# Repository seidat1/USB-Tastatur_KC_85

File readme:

#USB to KC 85

Dies ist ein Adapter, um eine USB-Tastatur an einen KC 85/2..5 anzuschließen.
Es ist mit diesem Adapter auch möglich ein Bluethoos-Tastatur zu betreiben.
Am KC 85 ist keine Änderung notwendig. Es werden die Signale der Originaltastatur nachgebildet.
Dies ergibt eine Flexibilität, wie sie bei der bisherigen Tastatur nicht möglich war. Jeder Taste und jeder Tastenkombination kann ein beliebiges Zeichen oder sogar beliebige Zeichenketten mit Steuerzeichen zugeordnet werden.

Grundlage dieses Adapters ist ein WEMOS D1 mini, der einen ESP8266 Mikroprozessor beinhaltet.
Der USB-Anschluss wird mit einem USB-Host Shield realisiert. 

Die Tastatursignale werden per USB an den USB-Host-Adapter gesendet und von dort per SPI an den Mikroprozessor weitergeleitet. Dieser erzeugt dann das Signal der KC-Tastatur und gibt dieses an den Tastaturstecker ab.
Die Tastencodes und Zeichenketten sind in einer Tastaturtabelle hinterlegt. Diese hat folgenden Aufbau:
	# große Buchstaben
	[CharTable]		# char 'A'
	KeyCnt	= 0x02
	CntMask	= 0xFF
	KeyCode	= 0x04
	Strg	= "A"
	.
	.
	.

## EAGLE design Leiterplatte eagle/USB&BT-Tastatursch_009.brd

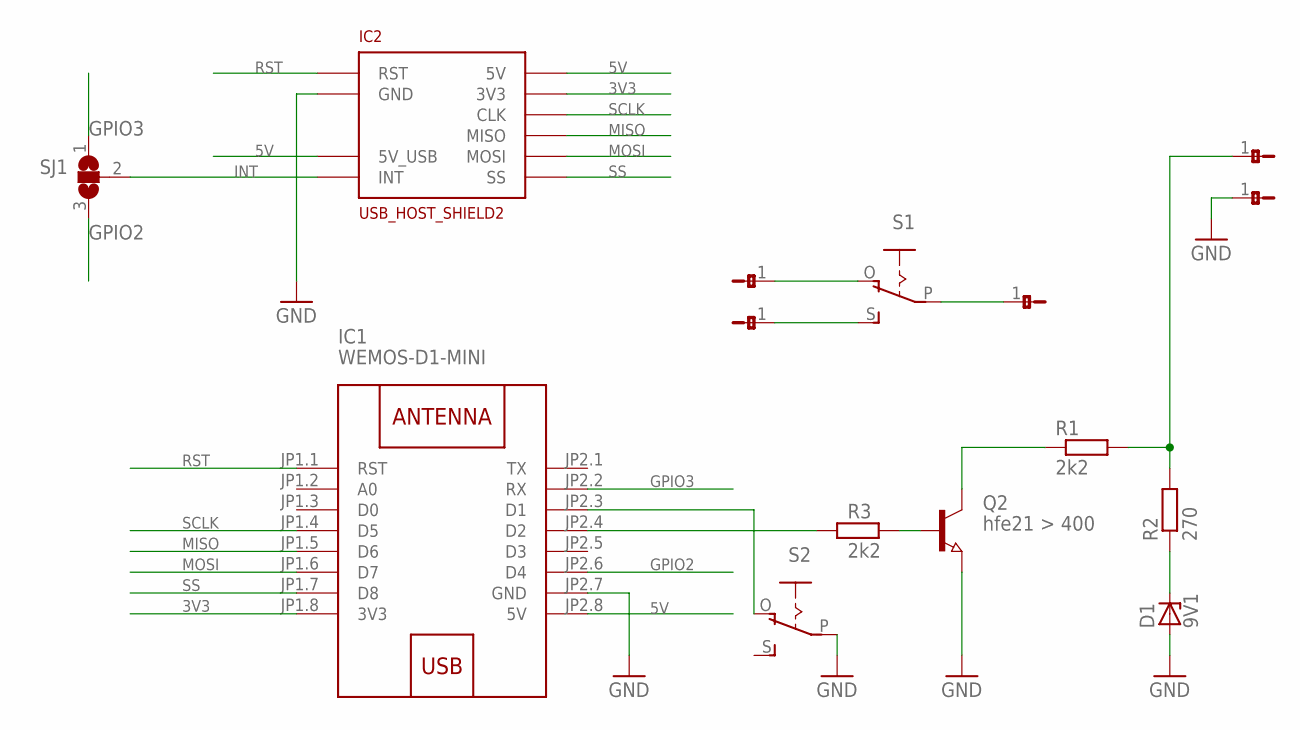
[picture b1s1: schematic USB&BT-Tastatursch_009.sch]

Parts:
D1: 9V1; DO34Z7
IC1: WEMOS-D1-MINI; WEMOS-D1-MINI_PUR
IC2: USB_HOST_SHIELD2; USB_HOST_SHIELD_2
Q2: hfe21 > 400; SOT23W
R1, R3: 2k2; M0805
R2: 270; M0805
S1, S2: EG1218S; EG1218
SJ1: SJ2WSJ_2B; SJ_2B
U$2, U$3, U$4, U$5, U$6: JP1-1JP1-1C; JP1-1C

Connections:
3V3: IC1.JP1.8 (3V3), IC2.VCC (3V3)
5V: IC1.JP2.8 (5V), IC2.5V, IC2.5V_USB
GND: D1.A, IC1.JP2.7 (GND), IC2.GND, IC2.GND@1 (GND), Q2.3 (E), S2.P, U$3.1
GPIO2: IC1.JP2.6 (D4), SJ1.3
GPIO3: IC1.JP2.2 (RX), SJ1.1
INT: IC2.INT, SJ1.2
MISO: IC1.JP1.5 (D6), IC2.MISO
MOSI: IC1.JP1.6 (D7), IC2.MOSI
unnamed: IC1.JP2.3 (D1), S2.O
unnamed: IC1.JP2.4 (D2), R3.1
unnamed: R1.2, R2.2, U$2.1
unnamed: D1.C, R2.1
unnamed: Q2.2 (C), R1.1
unnamed: S1.P, U$4.1
unnamed: S1.S, U$6.1
unnamed: Q2.1 (B), R3.2
unnamed: S1.O, U$5.1
RST: IC1.JP1.1 (RST), IC2.RST, IC2.RST@1 (RST)
SCLK: IC1.JP1.4 (D5), IC2.CLK
SS: IC1.JP1.7 (D8), IC2.SS

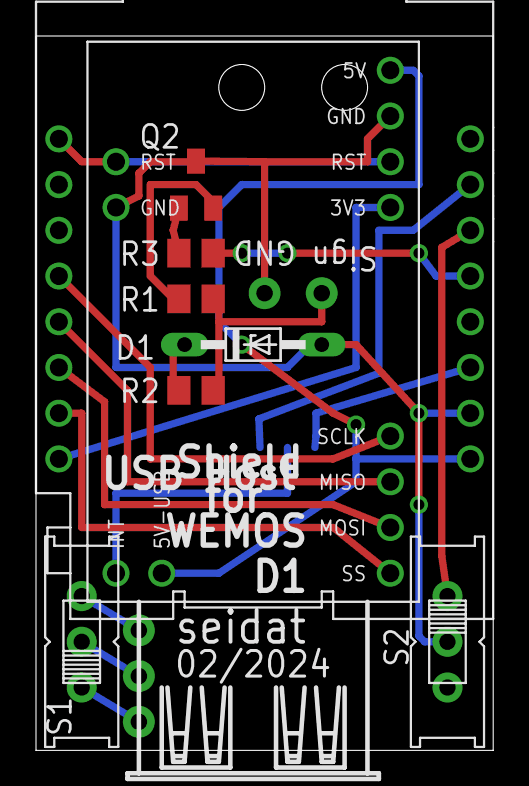
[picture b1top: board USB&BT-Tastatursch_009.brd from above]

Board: 2 copper layers, 25.4 x 39.7 mm, 15 parts (1 on the bottom side), 20 nets.

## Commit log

2024-03-29 no message

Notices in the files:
parts and their libraries:
diy-modules: Released under the Creative Commons Attribution 4.0 International License: http://creativecommons.org/licenses/by/4.0
